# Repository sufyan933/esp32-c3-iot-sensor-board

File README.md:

# Custom ESP32-C3 IoT Sensor Board

A professional, high-reliability 4-layer IoT edge platform designed end-to-end in KiCad. This board consolidates multi-sensor environmental telemetry, secure local storage, and intelligent Li-ion battery management around a RISC-V core.

---

## Technical Overview

The **ESP32-C3 IoT Sensor Board** is an ultra-compact, production-grade hardware platform built around the **ESP32-C3-WROOM-02** module. Designed to bridge the gap between benchtop breadboard prototypes and ruggedized field deployments, it integrates multi-domain sensing (atmospheric, acoustic, and luminous), redundant high-speed local storage, and a robust power management front-end onto a tightly constrained 4-layer stack-up.

### Subsystem Architecture

The board is architected with modular robustness in mind. Rather than relying on generic breakouts, every component is integrated directly onto the PCB, adhering to proper impedance matching, signal decoupling, and low-noise analog routing guidelines.

| Subsystem | Silicon / Component | Technical Specifications & Role |
| :--- | :--- | :--- |
| **MCU & Radio** | ESP32-C3-WROOM-02-H4 | 32-bit RISC-V single-core processor @ 160 MHz, integrated 2.4 GHz Wi-Fi & BLE 5.0 |
| **USB-UART Bridge**| CP2102N-A02-GQFN20 | High-speed data transit up to 3 Mbps; hardware flow control for automated flashing |
| **Power Path / Charger** | NCP73871-2CAI/WL | Linear Li-ion charge management with programmable thermal regulation & status pins |
| **LDO Regulator** | LML1117MPX-3.3 | High-efficiency 5 V to 3.3 V LDO supplying up to 800 mA to critical RF & sensor rails |
| **Atmospheric Sensing** | BME280 | Ultra-low power digital sensor for temperature, relative humidity, and barometric pressure |
| **Luminous Sensing** | TEMT6000X01 | Silicon NPN phototransistor matching human eye spectral sensitivity for ambient light sensing |
| **Acoustic Sensing** | MAX4466EXK + Mic | Electret condenser microphone paired with a rail-to-rail op-amp boasting adjustable gain |
| **Onboard Storage** | W25Q32JVSSIQ | 32 Mbit SPI NOR Flash dedicated to structured logging, failsafe firmware, or local databases |
| **Removable Storage** | microSD Socket | SPI-driven MicroSD card slot for bulk data logging and local diagnostic storage |

---

## Schematic Design

The electrical schematics are strategically partitioned across four clean, highly readable sheets. This modular organization ensures that power domains, high-frequency digital buses, and sensitive analog signals are isolated systematically.

* **Power & Root Management:** Incorporates a robust ESD-protected USB-C interface, the NCP73871 battery charger with charge/standby visual indicators, a dedicated Li-ion JST terminal, and a thermal-regulation-backed LDO stage delivering a clean 3.3V rail.
* **Core Processing & Storage:** Centers around the ESP32-C3 module, complete with vital decoupling networks, standard strapping resistor configurations, the CP2102N UART bridge, and dual SPI storage options (NOR flash and microSD).
* **Analog & Digital Sensors:** Interfaces the digital BME280 over an optimized I2C bus alongside the TEMT6000 light-intensity circuit and the high-gain MAX4466 microphone pre-amplifier network.
* **User Interface & Diagnostics:** Houses a dedicated I2C OLED display breakout, physical user tactile inputs (Boot & Reset), a GPIO expansion rail, and the standard dual-transistor auto-program/reset circuitry.

---

## PCB Stack-Up & Layout Philosophy

Designing an RF-enabled IoT board requires strict attention to electromagnetic compatibility (EMC) and signal integrity. A **4-layer PCB stack-up** was selected to achieve a continuous, unbroken reference ground plane directly beneath high-speed signals, mitigating crosstalk and RF return-path issues.

### Layout Highlights
* **RF Optimization:** The ESP32-C3’s onboard PCB antenna is positioned over a complete copper keep-out zone extending through all four layers of the board edge to maximize wireless transmission efficiency and range.
* **Signal Isolation:** Sensitive analog trace runs from the MAX4466 microphone amplifier are physically isolated from high-speed digital SPI lines and shielded by localized ground pours to prevent digital switching noise coupling into the audio stream.
* **Power Distribution Network (PDN):** Star-routing configurations and low-ESR ceramic decoupling capacitors located immediately adjacent to IC power pins ensure a highly stable power delivery network, dampening transient spikes during RF transmission bursts.

<table>
  <tr>
    <td align="center"><br/><sub><b>Layer 1: Front Copper (RF, Signals & High-Current Traces)</b></sub></td>
    <td align="center"><br/><sub><b>Layer 2: Inner Ground (Solid Reference Plane)</b></sub></td>
  </tr>
  <tr>
    <td align="center"><br/><sub><b>Layer 3: Inner Power (Split VCC_3V3 & VBUS Planes)</b></sub></td>
    <td align="center"><br/><sub><b>Layer 4: Back Copper (Secondary Signal Routing)</b></sub></td>
  </tr>
</table>

---

## Mechanical & 3D Verification

3D modeling was executed concurrently with routing inside KiCad's mechanical viewer. This physical validation ensured precise vertical clearance profiles for all discrete components, verified JST battery plug and USB-C port accessibility, and guaranteed seamless physical integration with custom-designed 3D-printed or injection-molded enclosures.

<table>
  <tr>
    <td align="center"><br/><sub><b>Front Orthographic Assembly</b></sub></td>
    <td align="center"><br/><sub><b>Back Orthographic Assembly</b></sub></td>
  </tr>
</table>

*Perspective render showcasing mechanical profile heights, component density, and silkscreen alignment.*

---

## Pinout and Connector Interfaces

### J4 — External OLED Header (I2C)
Provides a direct plug-and-play interface for small-form-factor I2C display panels (e.g., SSD1306) to show local telemetry in real time.

| Pin | Physical Designation | Signal Line | Description |
| :---: | :---: | :---: | :--- |
| **1** | GND | Ground | Main system ground reference |
| **2** | SCL | GPIO9 / SCL | I2C Serial Clock (10k pull-up onboard) |
| **3** | SDA | GPIO8 / SDA | I2C Serial Data (10k pull-up onboard) |
| **4** | 3.3V | VCC_3V3 | Cleaned 3.3V system power rail |

### J5 — GPIO Expansion Port
A secondary breakout header designed for system expansion, enabling the integration of external actuator modules, relay controls, or extra sensors.

| Pin | Physical Designation | Signal Line | Description |
| :---: | :---: | :---: | :--- |
| **1** | GND | Ground | Main system ground reference |
| **2** | IO19 | GPIO19 | General-purpose digital Input/Output |
| **3** | IO18 | GPIO18 | General-purpose digital Input/Output |
| **4** | IO8 | GPIO8 | General-purpose digital Input/Output |
| **5** | 3.3V | VCC_3V3 | Cleaned 3.3V system power rail |

### High-Speed SPI Diagnostics Test Points
Dedicated copper test pads are located on the PCB surface for logic analyzer debugging of the high-speed shared SPI bus. These permit painless monitoring of communication traffic between the MCU, the flash storage chip, and the microSD card.

| Test Point | Signal | Target Subsystem |
| :---: | :---: | :---: |
| **TP1** | MOSI | Master Out Slave In (Shared Bus) |
| **TP2** | MISO | Master In Slave Out (Shared Bus) |
| **TP3** | SCLK | Serial Clock (Shared Bus) |
| **TP4** | CS_SD | Chip Select (microSD Card) |
| **TP5** | CS_FL | Chip Select (NOR Flash) |

---

## Design and Operational Features

* **Auto-Program/Auto-Reset Circuitry:** Dual NPN-transistor auto-flashing logic allows seamless firmware uploads directly from any modern IDE (such as PlatformIO or the Arduino IDE) with a single click. There is no need to perform awkward button presses on the physical unit during flash compile sequences.
* **Bus Arbitration Resilience:** The SPI storage architecture uses dedicated, decoupled Chip Select lines (`CS_SD` and `CS_FL`) allowing the firmware to securely coordinate and multiplex operations between high-capacity, slow microSD card filesystem writes and fast, structured onboard NOR flash database logs.
* **Low-Noise Ground Isolation:** Features specialized split ground planes with a single-point bridge connection (star ground topology) to prevent switching transient noise generated by the ESP32-C3 radio from corrupting the highly sensitive analog input signal of the microphone op-amp stage.

---

## Applications

* **Localized Microclimate Monitoring:** Secure logging of humidity, barometric pressure, and temperature variations over long time horizons.
* **Industrial Noise & Light Level Logging:** Real-time logging of acoustic noise thresholds and lighting conditions for factory floor safety and auditing.
* **Field Prototyping Platform:** A robust, reliable alternative to unstable breadboard and jumper-wire setups for rapid IoT firmware validation under realistic battery-powered situations.

---

## Author

Designed and maintained by:

**Muhammad Sufyan** Electrical Engineering Department  
*Pakistan Institute of Engineering and Applied Sciences (PIEAS)* [LinkedIn](#) · [GitHub](#)

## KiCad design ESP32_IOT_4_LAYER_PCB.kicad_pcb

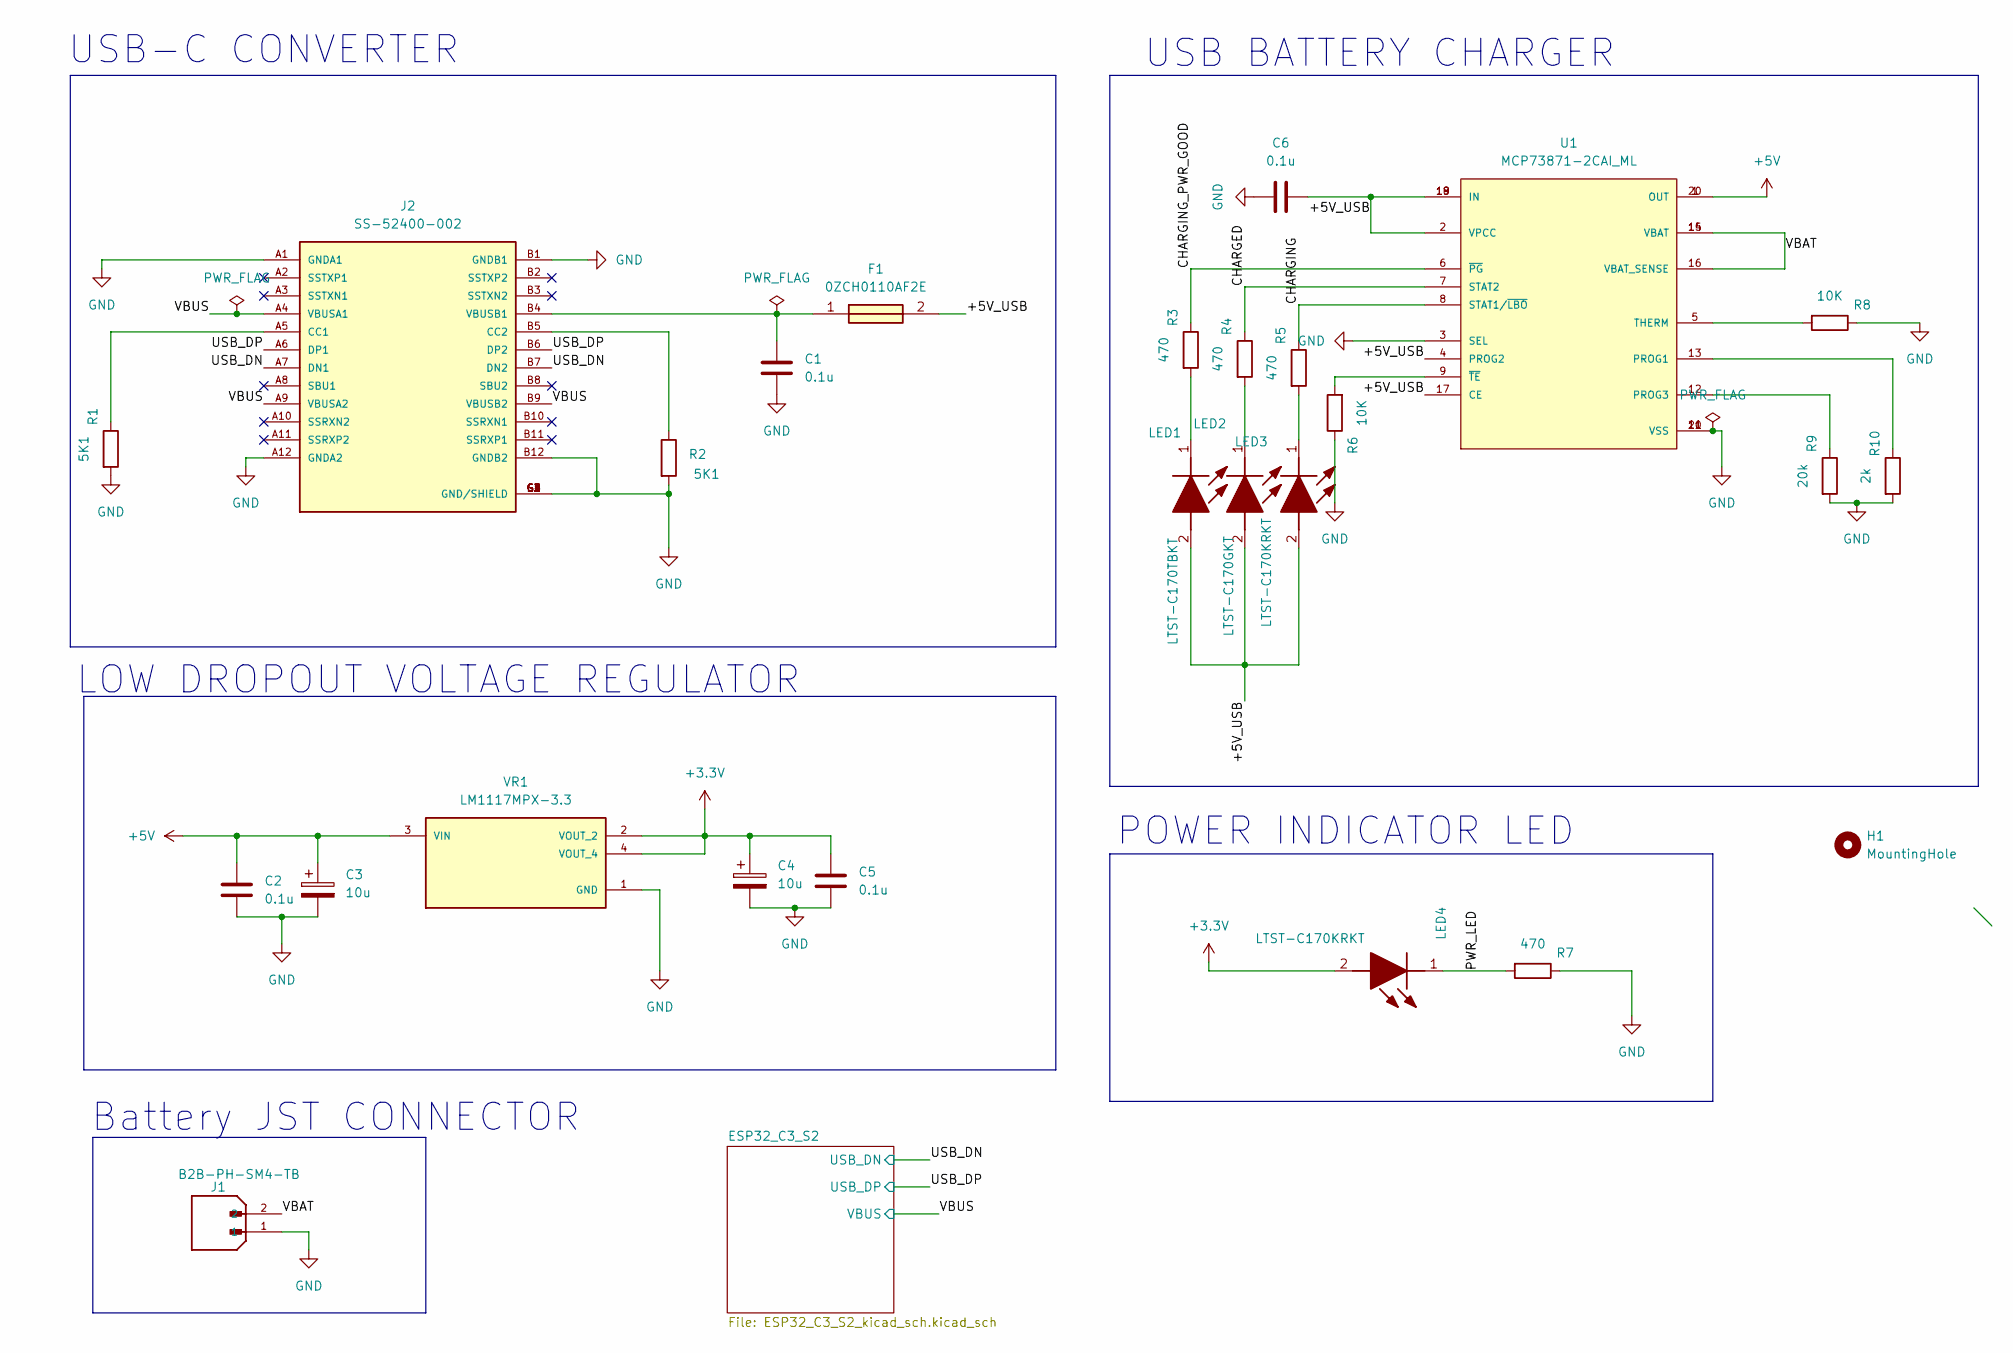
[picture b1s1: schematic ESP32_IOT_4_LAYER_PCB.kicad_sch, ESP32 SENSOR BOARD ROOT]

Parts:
C1, C2, C5, C6: 0.1u; C_0805_2012Metric
C3, C4: 10u; T491A
F1: 0ZCH0110AF2E; FUSC3226X100N; Manufacturer_Part_Number 0ZCH0110AF2E
H1: MountingHole; MountingHole_2.5mm
J1: B2B-PH-SM4-TB; JST_B2B-PH-SM4-TB; PARTREV N/A
J2: SS-52400-002; BELFUSE_SS-52400-002; PARTREV A0
LED1: LTST-C170TBKT; LEDC2012X120N; Manufacturer_Part_Number LTST-C170TBKT; Mouser Part Number 859-LTST-C170TBKT
LED2: LTST-C170GKT; LEDC2012X120N; Manufacturer_Part_Number LTST-C170GKT; Mouser Part Number 859-LTST-C170GKT
LED3, LED4: LTST-C170KRKT; LEDC2012X120N; Manufacturer_Part_Number LTST-C170KRKT; Mouser Part Number 859-LTST-C170KRKT
R1, R2: 5K1; R_0805_2012Metric
R3, R4, R5, R7: 470; R_0805_2012Metric
R6, R8: 10K; R_0805_2012Metric
R9: 20k; R_0805_2012Metric
R10: 2k; R_0805_2012Metric
U1: MCP73871-2CAI_ML; QFN50P400X400X100-21N; PARTREV D
VR1: LM1117MPX-3.3; VREG_LM1117MPX-3.3

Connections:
+3.3V: C4.1, C5.1, LED4.2 (A), VR1.2 (VOUT_2), VR1.4 (VOUT_4); also elsewhere on the board
+5V: C2.1, C3.1, U1.1 (OUT), U1.20 (OUT), VR1.3 (VIN)
/+5V_USB: C6.1, F1.2, LED1.2 (A), LED2.2 (A), LED3.2 (A), U1.2 (VPCC), U1.4 (PROG2), U1.17 (CE), U1.18 (IN), U1.19 (IN)
/CHARGED: R4.1, U1.7 (STAT2)
/CHARGING: R5.1, U1.8 (STAT1/~LBO)
/CHARGING_PWR_GOOD: R3.1, U1.6 (~PG)
/PWR_LED: LED4.1 (K), R7.2
/USB_DN: J2.A7 (DN1), J2.B7 (DN2); also elsewhere on the board
/USB_DP: J2.A6 (DP1), J2.B6 (DP2); also elsewhere on the board
/VBAT: J1.2, U1.14 (VBAT), U1.15 (VBAT), U1.16 (VBAT_SENSE)
/VBUS: J2.A4 (VBUSA1), J2.A9 (VBUSA2), J2.B9 (VBUSB2); also elsewhere on the board
GND: C1.2, C2.2, C3.2, C4.2, C5.2, C6.2, J1.1, J2.A1 (GNDA1), J2.A12 (GNDA2), J2.B1 (GNDB1), J2.B12 (GNDB2), J2.G1 (GND/SHIELD), J2.G2 (GND/SHIELD), J2.G3 (GND/SHIELD), J2.G4 (GND/SHIELD), J2.S1 (GND/SHIELD), J2.S2 (GND/SHIELD), J2.S3 (GND/SHIELD), J2.S4 (GND/SHIELD), R1.2, R2.2, R6.1, R7.1, R8.1, R9.2, R10.2, U1.3 (SEL), U1.10 (VSS), U1.11 (VSS), U1.21 (VSS), VR1.1 (GND); also elsewhere on the board
unnamed: J2.A5 (CC1), R1.1
unnamed: J2.B5 (CC2), R2.1
unnamed: C1.1, F1.1, J2.B4 (VBUSB1)
unnamed: LED1.1 (K), R3.2
unnamed: LED2.1 (K), R4.2
unnamed: LED3.1 (K), R5.2
unnamed: R10.1, U1.13 (PROG1)
unnamed: R9.1, U1.12 (PROG3)
unnamed: R8.2, U1.5 (THERM)
unnamed: R6.2, U1.9 (~TE)

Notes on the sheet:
POWER INDICATOR LED
Battery JST CONNECTOR
USB BATTERY CHARGER
USB-C CONVERTER
LOW DROPOUT VOLTAGE REGULATOR

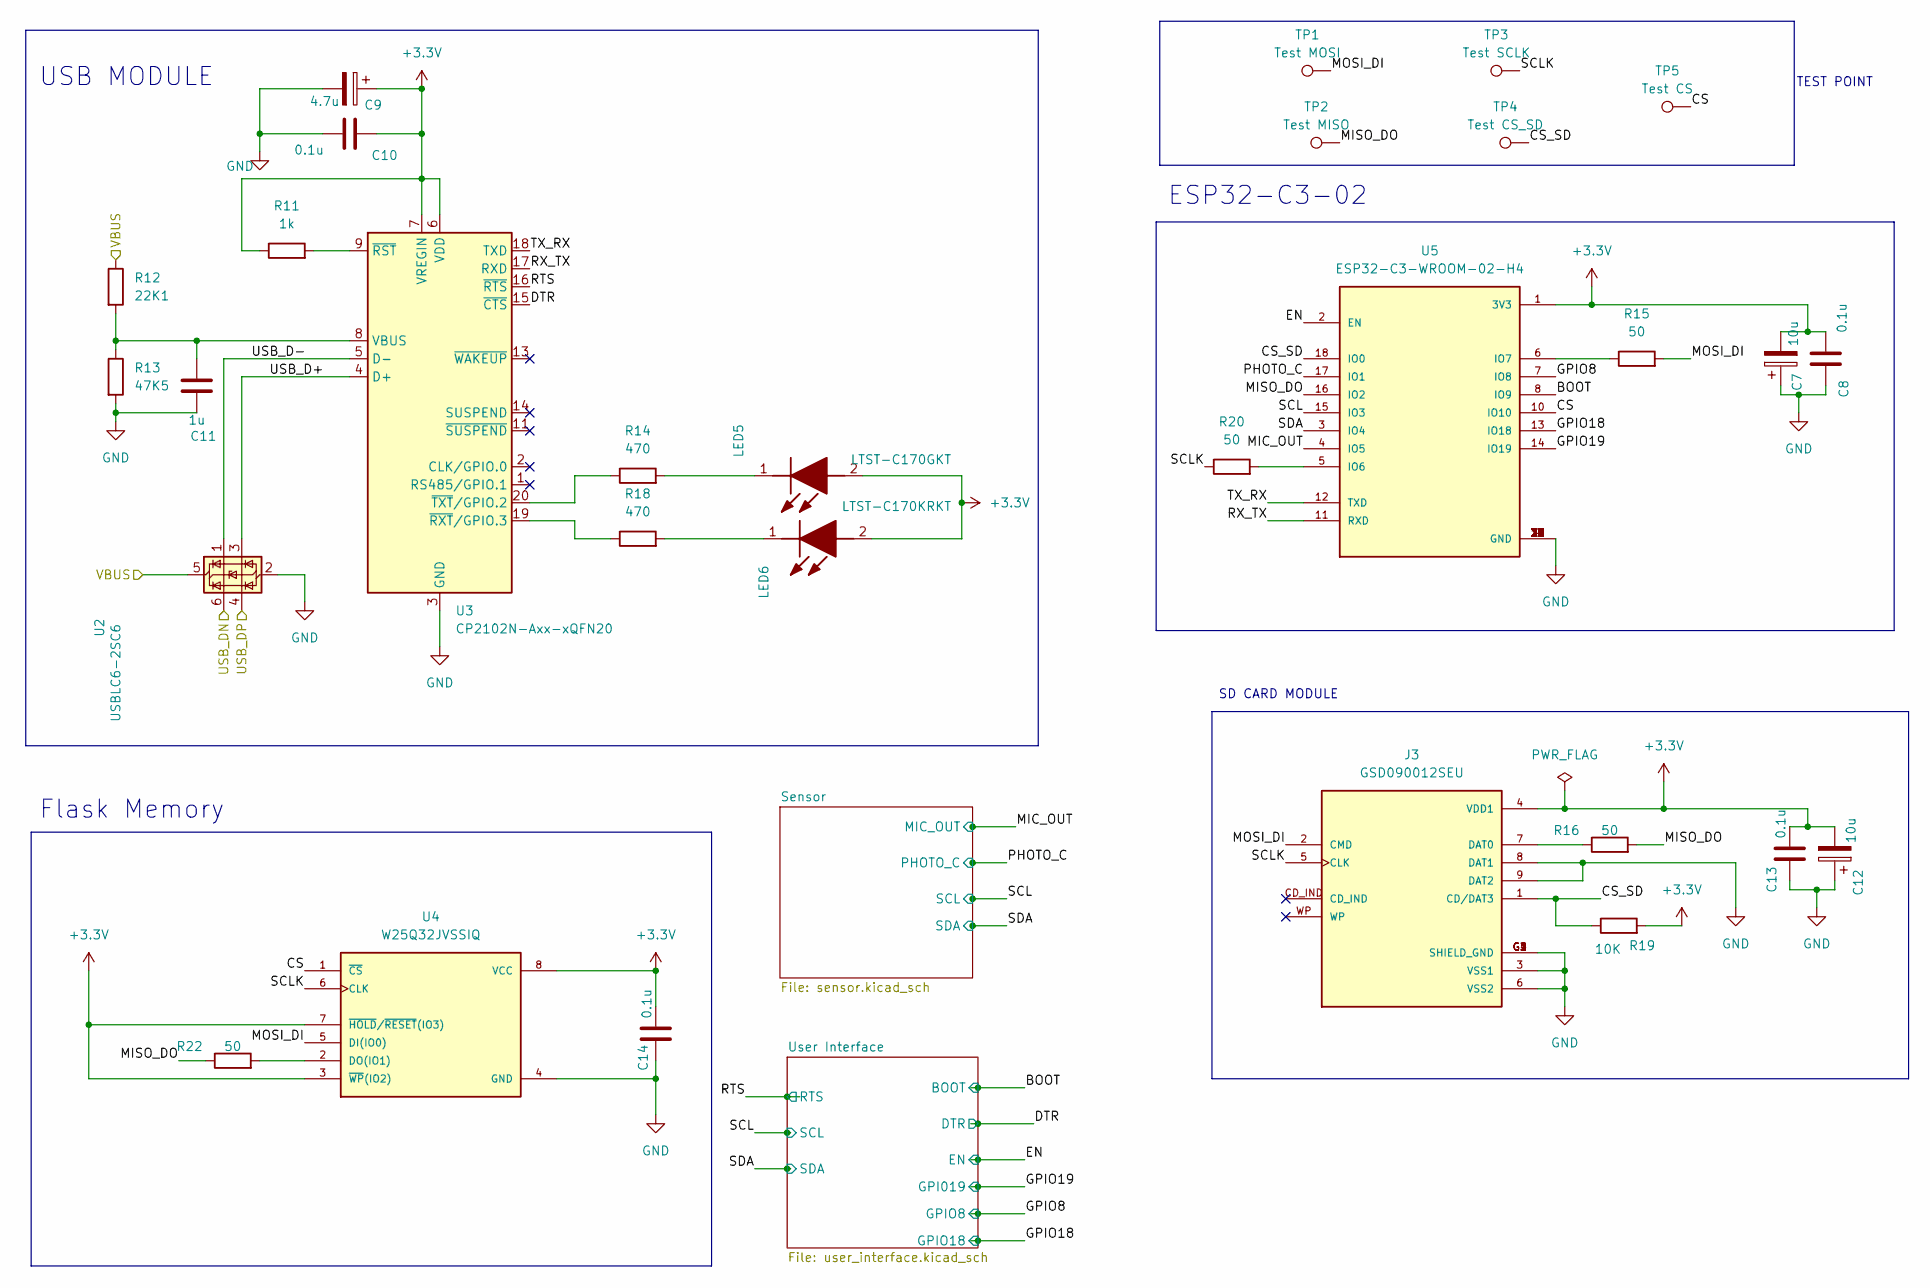
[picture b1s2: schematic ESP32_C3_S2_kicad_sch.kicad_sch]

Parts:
C7, C12: 10u; T491A
C8, C10, C13, C14: 0.1u; C_0805_2012Metric
C9: 4.7u; T491A
C11: 1u; C_0805_2012Metric
J3: GSD090012SEU; AMPHENOL_GSD090012SEU; PARTREV E
LED5: LTST-C170GKT; LEDC2012X120N; Manufacturer_Part_Number LTST-C170GKT; Mouser Part Number 859-LTST-C170GKT
LED6: LTST-C170KRKT; LEDC2012X120N; Manufacturer_Part_Number LTST-C170KRKT; Mouser Part Number 859-LTST-C170KRKT
R11: 1k; R_0805_2012Metric
R12: 22K1; R_0805_2012Metric
R13: 47K5; R_0805_2012Metric
R14, R18: 470; R_0805_2012Metric
R15, R16, R20, R22: 50; R_0805_2012Metric
R19: 10K; R_0805_2012Metric
TP1: Test MOSI; TestPoint_Pad_D1.0mm
TP2: Test MISO; TestPoint_Pad_D1.0mm
TP3: Test SCLK; TestPoint_Pad_D1.0mm
TP4: Test CS_SD; TestPoint_Pad_D1.0mm
TP5: Test CS; TestPoint_Pad_D1.0mm
U2: USBLC6-2SC6; SOT-23-6
U3: CP2102N-Axx-xQFN20; QFN50P400X400X100-21N
U4: W25Q32JVSSIQ; SOIC127P790X216-8N; M_PART_NUMBER W25QXX
U5: ESP32-C3-WROOM-02-H4; MODULE_ESP32-C3-WROOM-02-H4

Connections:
+3.3V: C7.2, C8.1, C9.1, C10.2, C12.2, C13.1, C14.1, J3.4 (VDD1), LED5.2 (A), LED6.2 (A), R11.1, R19.2, U3.6 (VDD), U3.7 (VREGIN), U4.3 (~WP(IO2)), U4.7 (~HOLD/~RESET(IO3)), U4.8 (VCC), U5.1 (3V3); also elsewhere on the board
/ESP32_C3_S2/BOOT: U5.8 (IO9); also elsewhere on the board
/ESP32_C3_S2/CS: TP5.1 (1_1), U4.1 (~CS), U5.10 (IO10)
/ESP32_C3_S2/CS_SD: J3.1 (CD/DAT3), R19.1, TP4.1 (1_1), U5.18 (IO0)
/ESP32_C3_S2/DTR: U3.15 (~CTS); also elsewhere on the board
/ESP32_C3_S2/EN: U5.2 (EN); also elsewhere on the board
/ESP32_C3_S2/GPIO8: U5.7 (IO8); also elsewhere on the board
/ESP32_C3_S2/GPIO18: U5.13 (IO18); also elsewhere on the board
/ESP32_C3_S2/GPIO19: U5.14 (IO19); also elsewhere on the board
/ESP32_C3_S2/MIC_OUT: U5.4 (IO5); also elsewhere on the board
/ESP32_C3_S2/MISO_DO: R16.2, R22.1, TP2.1 (1_1), U5.16 (IO2)
/ESP32_C3_S2/MOSI_DI: J3.2 (CMD), R15.2, TP1.1 (1_1), U4.5 (DI(IO0))
/ESP32_C3_S2/PHOTO_C: U5.17 (IO1); also elsewhere on the board
/ESP32_C3_S2/RTS: U3.16 (~RTS); also elsewhere on the board
/ESP32_C3_S2/RX_TX: U3.17 (RXD), U5.11 (RXD)
/ESP32_C3_S2/SCL: U5.15 (IO3); also elsewhere on the board
/ESP32_C3_S2/SCLK: J3.5 (CLK), R20.1, TP3.1 (1_1), U4.6 (CLK)
/ESP32_C3_S2/SDA: U5.3 (IO4); also elsewhere on the board
/ESP32_C3_S2/TX_RX: U3.18 (TXD), U5.12 (TXD)
/ESP32_C3_S2/USB_D+: U2.3 (I/O2), U3.4 (D+)
/ESP32_C3_S2/USB_D-: U2.1 (I/O1), U3.5 (D-)
/USB_DN: U2.6 (I/O1); also elsewhere on the board
/USB_DP: U2.4 (I/O2); also elsewhere on the board
/VBUS: R12.1, U2.5 (VBUS); also elsewhere on the board
GND: C7.1, C8.2, C9.2, C10.1, C11.2, C12.1, C13.2, C14.2, J3.3 (VSS1), J3.6 (VSS2), J3.8 (DAT1), J3.9 (DAT2), J3.G1 (SHIELD_GND), J3.G2 (SHIELD_GND), J3.G3 (SHIELD_GND), J3.G4 (SHIELD_GND), R13.2, U2.2 (GND), U3.3 (GND), U3.12 (GND), U3.21 (GND), U4.4 (GND), U5.9 (GND), U5.19 (GND), U5.20 (GND), U5.21 (GND), U5.22 (GND), U5.23 (GND), U5.24 (GND), U5.25 (GND), U5.26 (GND), U5.27 (GND), U5.28 (GND), U5.29 (GND), U5.30 (GND), U5.31 (GND), U5.32 (GND), U5.33 (GND), U5.34 (GND), U5.35 (GND), U5.36 (GND), U5.37 (GND), U5.38 (GND), U5.39 (GND); also elsewhere on the board
unnamed: J3.7 (DAT0), R16.1
unnamed: LED5.1 (K), R14.2
unnamed: LED6.1 (K), R18.2
unnamed: C11.1, R12.2, R13.1, U3.8 (VBUS)
unnamed: R11.2, U3.9 (~RST)
unnamed: R18.1, U3.19 (~RXT/GPIO.3)
unnamed: R14.1, U3.20 (~TXT/GPIO.2)
unnamed: R22.2, U4.2 (DO(IO1))
unnamed: R20.2, U5.5 (IO6)
unnamed: R15.1, U5.6 (IO7)

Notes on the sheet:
TEST POINT
USB MODULE
SD CARD MODULE
Flask Memory
ESP32-C3-02

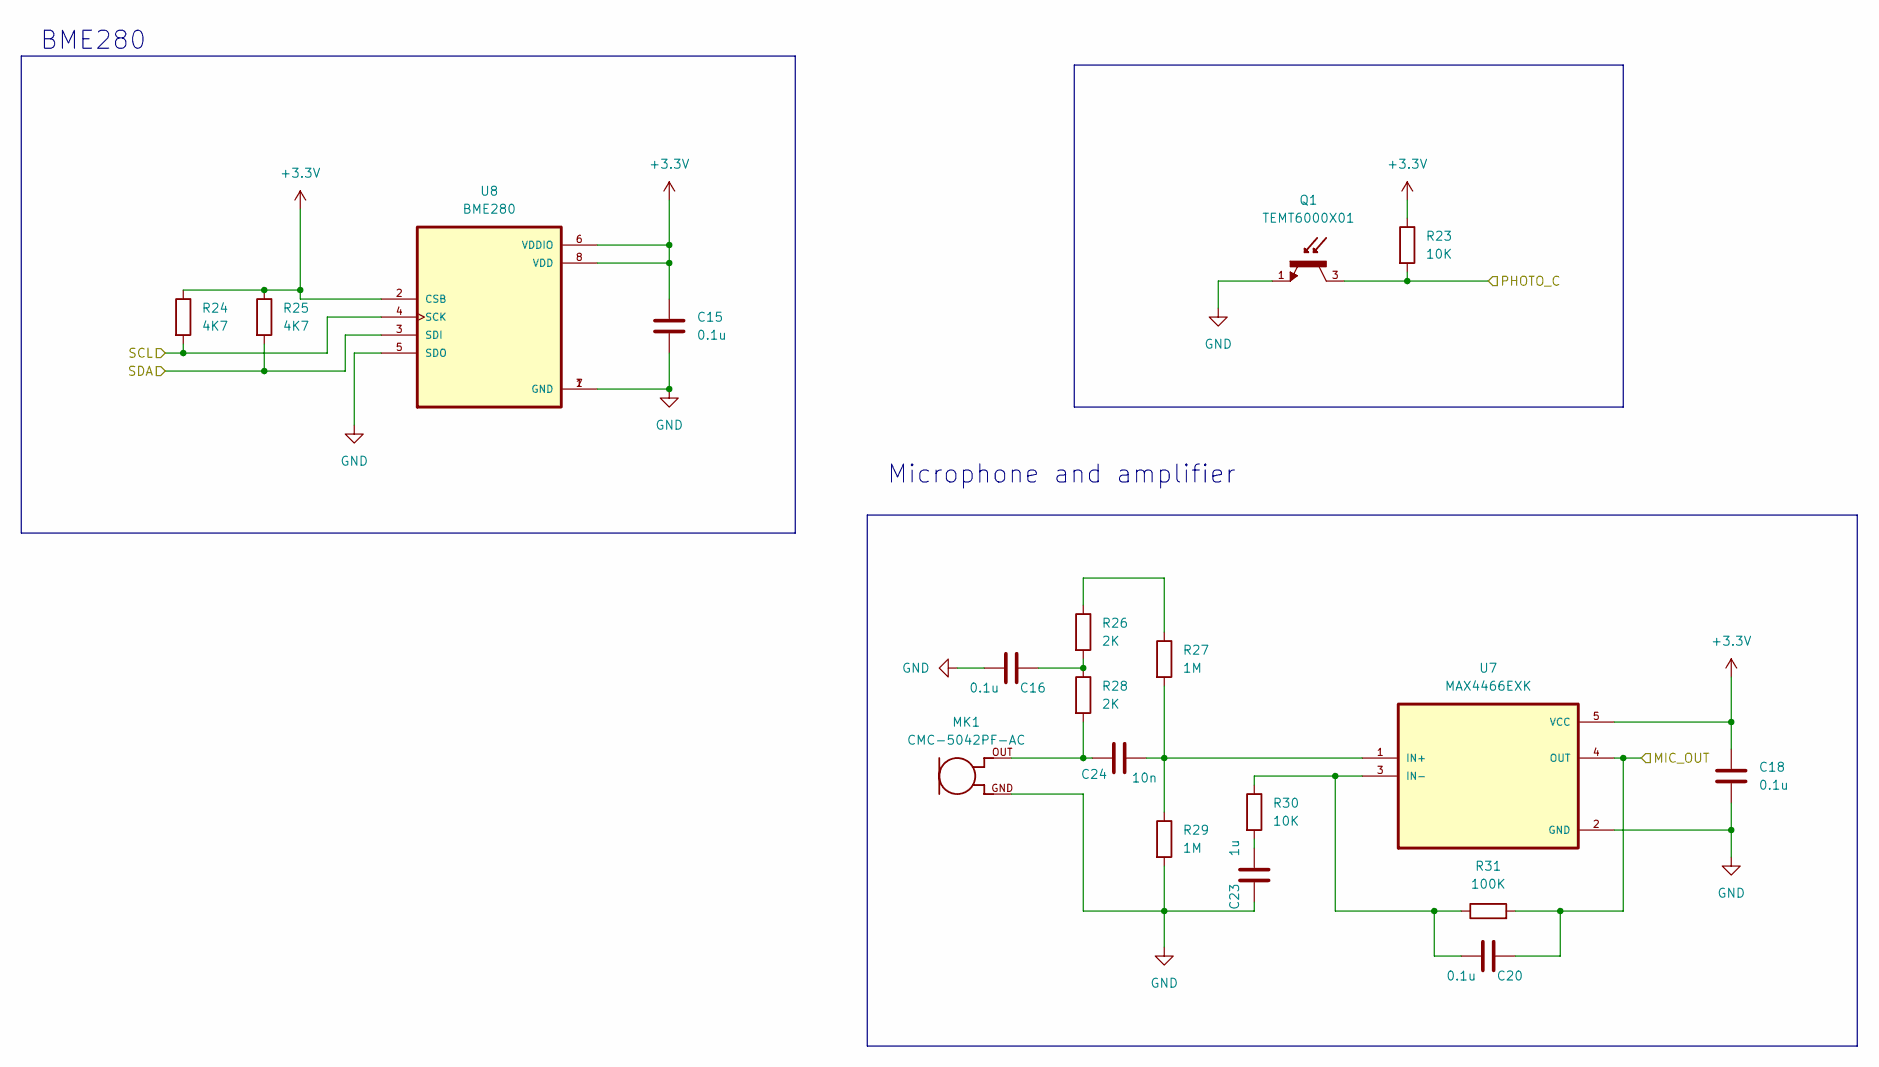
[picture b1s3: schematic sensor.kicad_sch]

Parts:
C15, C16, C18, C20: 0.1u; C_0805_2012Metric
C23: 1u; C_0805_2012Metric
C24: 10n; C_0805_2012Metric
MK1: CMC-5042PF-AC; CUI_CMC-5042PF-AC
Q1: TEMT6000X01; TRANS_TEMT6000X01; PARTREV 1.9
R23, R30: 10K; R_0805_2012Metric
R24, R25: 4K7; R_0805_2012Metric
R26, R28: 2K; R_0805_2012Metric
R27, R29: 1M; R_0805_2012Metric
R31: 100K; R_0805_2012Metric
U7: MAX4466EXK; SOT65P210X110-5N
U8: BME280; PSON65P250X250X100-8N

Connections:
+3.3V: C15.1, C18.1, R23.1, R24.1, R25.1, U7.5 (VCC), U8.2 (CSB), U8.6 (VDDIO), U8.8 (VDD); also elsewhere on the board
/ESP32_C3_S2/MIC_OUT: C20.1, R31.2, U7.4 (OUT); also elsewhere on the board
/ESP32_C3_S2/PHOTO_C: Q1.3, R23.2; also elsewhere on the board
/ESP32_C3_S2/SCL: R24.2, U8.4 (SCK); also elsewhere on the board
/ESP32_C3_S2/SDA: R25.2, U8.3 (SDI); also elsewhere on the board
GND: C15.2, C16.2, C18.2, C23.1, MK1.GND, Q1.1, R29.2, U7.2 (GND), U8.1 (GND), U8.5 (SDO), U8.7 (GND); also elsewhere on the board
unnamed: C16.1, R26.2, R28.1
unnamed: C23.2, R30.2
unnamed: C24.1, MK1.OUT, R28.2
unnamed: R26.1, R27.1
unnamed: C24.2, R27.2, R29.1, U7.1 (IN+)
unnamed: C20.2, R30.1, R31.1, U7.3 (IN-)

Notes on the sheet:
BME280
Microphone and amplifier

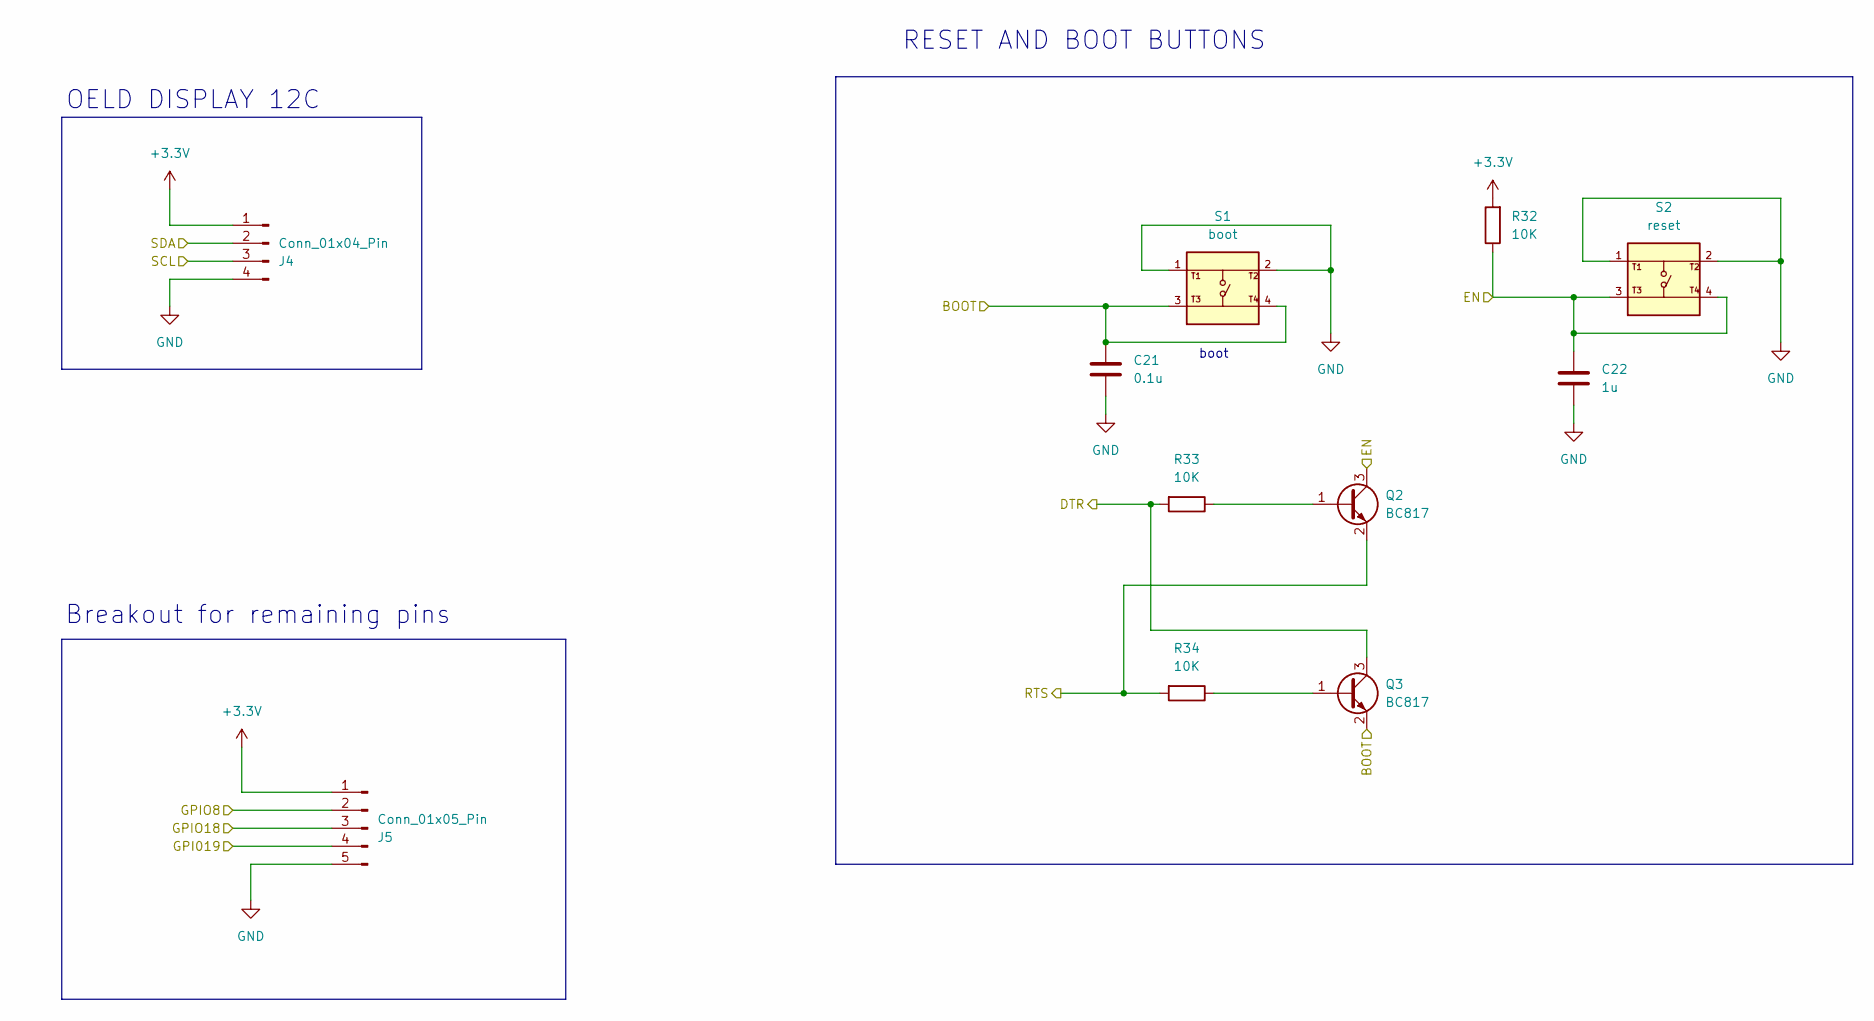
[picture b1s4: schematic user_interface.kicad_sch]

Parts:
C21: 0.1u; C_0805_2012Metric
C22: 1u; C_0805_2012Metric
J4: Conn_01x04_Pin; PinSocket_1x04_P2.54mm_Vertical
J5: Conn_01x05_Pin; PinSocket_1x05_P2.54mm_Vertical
Q2, Q3: BC817; SOT-23
R32, R33, R34: 10K; R_0805_2012Metric
S1: boot; SW_USLPT2819DT2TR; PARTREV P
S2: reset; SW_USLPT2819DT2TR; PARTREV P

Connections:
+3.3V: J4.1, J5.1, R32.2; also elsewhere on the board
/ESP32_C3_S2/BOOT: C21.1, Q3.2 (E), S1.3, S1.4; also elsewhere on the board
/ESP32_C3_S2/DTR: Q3.3 (C), R33.2; also elsewhere on the board
/ESP32_C3_S2/EN: C22.1, Q2.3 (C), R32.1, S2.3, S2.4; also elsewhere on the board
/ESP32_C3_S2/GPIO8: J5.2; also elsewhere on the board
/ESP32_C3_S2/GPIO18: J5.3; also elsewhere on the board
/ESP32_C3_S2/GPIO19: J5.4; also elsewhere on the board
/ESP32_C3_S2/RTS: Q2.2 (E), R34.2; also elsewhere on the board
/ESP32_C3_S2/SCL: J4.3; also elsewhere on the board
/ESP32_C3_S2/SDA: J4.2; also elsewhere on the board
GND: C21.2, C22.2, J4.4, J5.5, S1.1, S1.2, S2.1, S2.2; also elsewhere on the board
unnamed: Q2.1 (B), R33.1
unnamed: Q3.1 (B), R34.1

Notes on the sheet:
RESET AND BOOT BUTTONS
boot
Breakout for remaining pins
OELD DISPLAY 12C

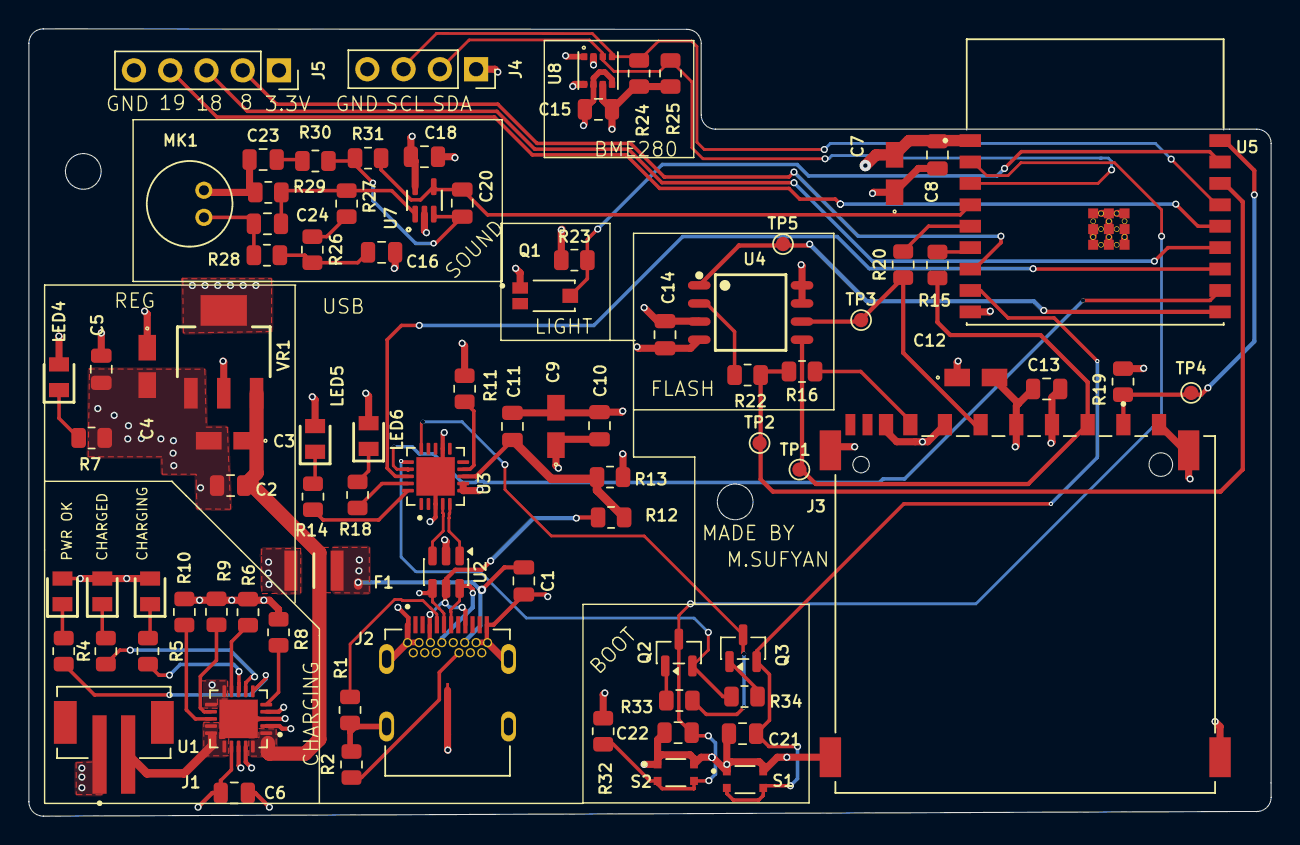
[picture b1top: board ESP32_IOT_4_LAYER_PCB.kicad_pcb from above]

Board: 4 copper layers, 87.0 x 55.2 mm, 87 parts (0 on the bottom side), 60 nets.

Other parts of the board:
H1#2: MountingHole; MountingHole_2.5mm
